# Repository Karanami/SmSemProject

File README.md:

# Piotr Lesicki 151052 - Line Follower

## General description
Line Follower - as it's name implies this robot will realise the task of following the line. 
The robot will consist of two motors, imu, line sensors (white/black color detectors), motor
encoders as well as an external data storage (flash/sd card) for data logging and of coures
it will also have an uC for general control.

## Hardware

### Motors & motor encoders
The robot will use a simple brushed motor with an extended shaft for the encoder feedback

### IMU
A six axis IMU will be used for data logging.

### line sensors
Basic refleted light detectors will be used for estimating where a black line on a white
background is.

### External data storage
A external storage in a form of a chip or a sd card will be used for logging

### uC
An STM32WB55RGVx will be used for the heart of the robot. It will also allow for a bluetooth
communication implementation to be included in the project, making the whole project smaller 
and more compact.

## Line Following task - regulator
The appropriate regulator is yet to be chosen

## Software

### RTOS 
For an easier implementation of software a fitting RTOS will be used. Azure RTOS will be used 
for that since it implements many robust sub-libraries allowing for light-weight aplications,
such as storage (file storage) drivers for external flash/sd cards or usb interfaces allowing
for on slave multiple devices implemantation and much more.
<br/> 

## Examples
- https://forbot.pl/blog/leksykon/robot-typu-linefollower
- https://www.jsumo.com/arduino-pid-based-line-follower-kit1

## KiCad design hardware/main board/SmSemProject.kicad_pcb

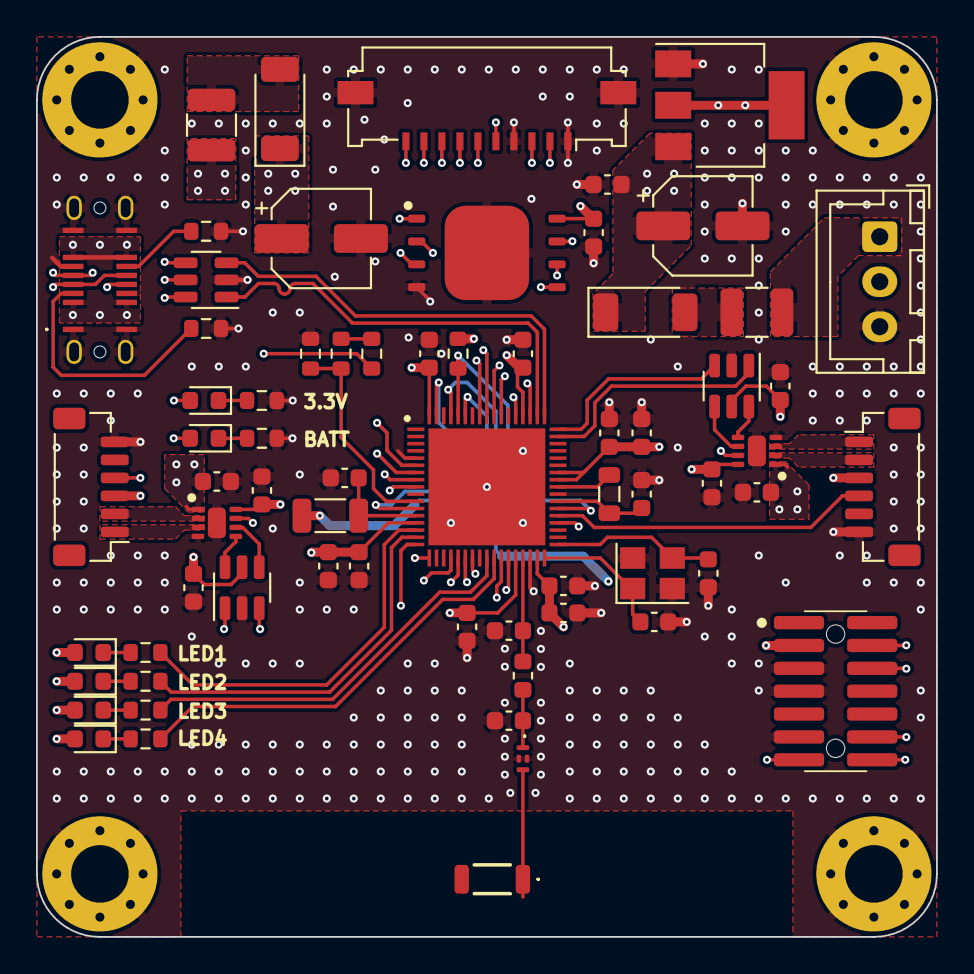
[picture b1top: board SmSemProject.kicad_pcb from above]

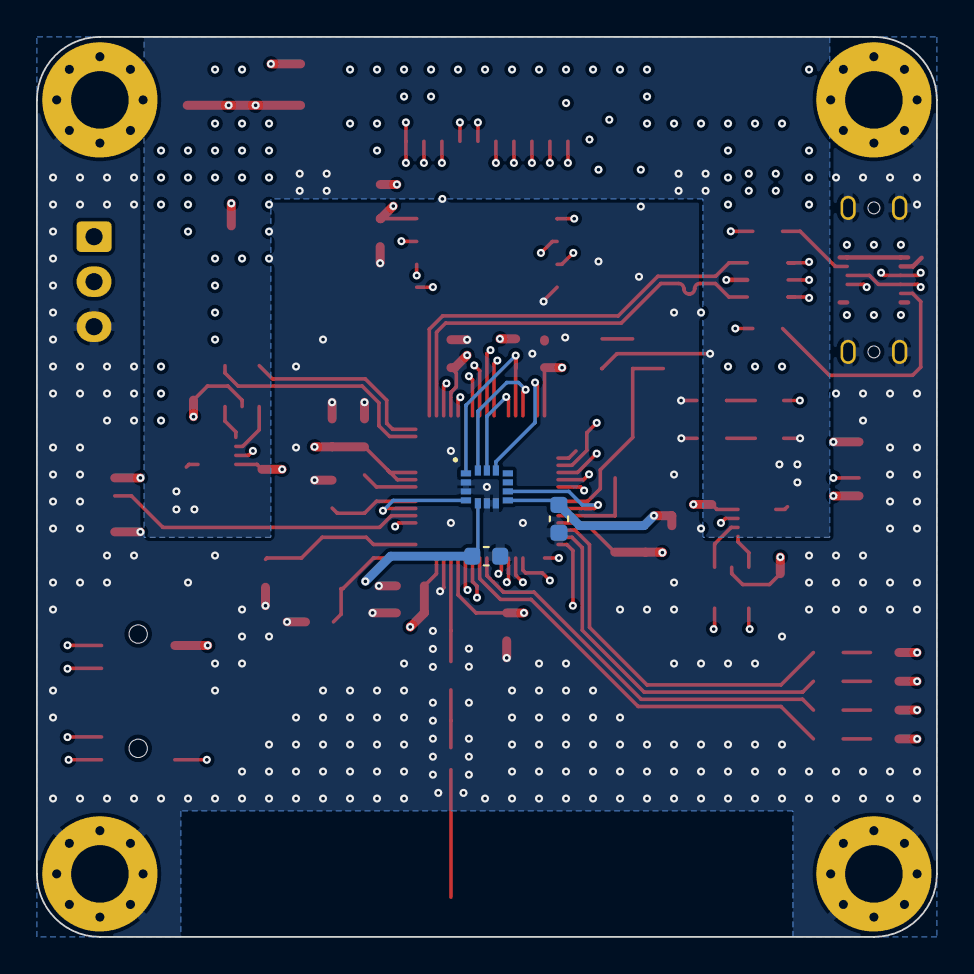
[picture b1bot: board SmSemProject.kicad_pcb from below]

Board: 8 copper layers, 50.0 x 50.0 mm, 74 parts (3 on the bottom side), 69 nets.

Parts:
ANT1: 74889302450
C1, C2: 20pF; C_0603_1608Metric
C3, C4, C5, C9, C11, C16, C19, C25, C26, C27, C28, C30, C31: 100nF; C_0603_1608Metric
C7: 10nF; C_0603_1608Metric
C8: 1uF; C_0603_1608Metric
C10: 100pF; C_0603_1608Metric
C13: 10uF; C_0603_1608Metric
C14, C15, C18, C24: 4.7uF; C_0603_1608Metric
C17, C29: 100uF; CP_Elec_5x4.5
C20: 0.3pF; C_0603_1608Metric
C21: 0.8pF; C_0603_1608Metric
D1, D3: RBS2LAM40CTR; D_SOD-128
D2, D4, D5, D6, D7, D8: LED_Small; LED_0603_1608Metric
F1, F2: 0.5A/16V; Fuse_1210_3225Metric
FL1: DLF162500LT-5028A1; DLF162500LT5028A1
H1, H2, H3, H4: MountingHole_Pad; MountingHole_3.2mm_M3_Pad_Via
IC1: STM32WB55RGV6; QFN40P800X800X100-69N-D
IC2, IC3: DRV8212PDSGR; SON50P200X200X80-9N
IC4: W25N01GVZEIG; SON127P800X600X80-9N-D
IC5: LSM6DSLTR
IC6, IC7: SN74LVC1G18DBVRG4; SOT-23-6
J1, J2: JST-SH 01x06; JST_SH_BM06B-SRSS-TB_1x06-1MP_P1.00mm_Vertical
J3: JST_XH_B3B; JST_XH_B3B-XH-A_1x03_P2.50mm_Vertical
J4: FTSH-107-01-L-DV-K-A; FTSH-107-XX-YYY-DV-K-A
J6: USB4145-03-0070-C; USB4145030070C
J7: Conn_01x10; Molex_200528-0100_1x10-1MP_P1.00mm_Horizontal
L1: 1mH; L_1206_3216Metric
L2: 74479774222; WE-PMI_080562
L3: 2.7nH; L_0603_1608Metric
R1: 1k; R_0603_1608Metric
R2, R3: 5.1k; R_0603_1608Metric
R4, R5, R6, R7, R8, R9, R10, R11, R12: 10k; R_0603_1608Metric
U1: LM1117MP-3.3; SOT-223-3_TabPin2
U2: USBLC6-2SC6; SOT-23-6
Y1: X322516MLB4SI; Crystal_SMD_3225-4Pin_3.2x2.5mm

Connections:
+3.3V: C3.2, C4.2, C5.2, C7.1, C8.1, C9.2, C10.2, C11.2, C15.1, C19.1, C25.1, C26.1, C27.2, C28.2, C30.1, C31.1, D2.2 (A), D4.2 (A), D5.2 (A), D6.2 (A), D7.2 (A), IC1.14 (VDDA), IC1.30 (VDD), IC1.33 (VDDRF), IC1.44 (VDDSMPS), IC1.45 (VDD), IC1.55 (VDDUSB), IC1.68 (VDD), IC2.8 (VCC), IC3.8 (VCC), IC4.8 (VCC), IC5.5 (VDDIO), IC5.8 (VDD), IC6.5 (VCC), IC7.5 (VCC), J1.3, J2.3, J4.3, J7.10, L1.1, R1.1, U1.2 (VO)
+BATT: C16.1, C17.1, C18.1, C24.1, C29.1, D1.1 (K), D3.1 (K), D8.2 (A), IC2.1 (VM), IC3.1 (VM), R9.2, U1.3 (VI)
/ANT_IN: ANT1.1 (FEED), FL1.3 (OUT)
/CONN_D+: J6.A6 (D+), J6.B6 (D+), U2.6 (I/O1)
/CONN_D-: J6.A7 (D-), J6.B7 (D-), U2.4 (I/O2)
/FLT_IN: C21.2, FL1.1 (IN), L3.2
/M_LEFT+: IC2.3 (OUT2), J2.1
/M_LEFT-: IC2.2 (OUT1), J2.2
/M_LEFT_A: IC1.9 (PC0), J2.4
/M_LEFT_DIRECTION: IC1.24 (PA9), IC7.1
/M_LEFT_PWM: IC1.23 (PA8), IC7.3
/M_RIGHT+: IC3.3 (OUT2), J1.1
/M_RIGHT-: IC3.2 (OUT1), J1.2
/M_RIGHT_A: IC1.39 (PB1), J1.4
/M_RIGHT_DIRECTION: IC1.50 (PC6), IC6.1
/M_RIGHT_PWM: IC1.51 (PA10), IC6.3
/Motor Control Left/PWMF: IC2.6 (IN1), IC7.4
/Motor Control Left/PWMR: IC2.5 (IN2), IC7.6
/Motor Control Left/~SLEEP: IC1.38 (PB0), IC2.7 (~SLEEP), IC3.7 (~SLEEP)
/Motor Control Right/PWMF: IC3.6 (IN1), IC6.4
/Motor Control Right/PWMR: IC3.5 (IN2), IC6.6
/SPI_CLK: IC1.63 (PB3), IC5.13 (SCL), J7.5
/SPI_EX_INT1: IC1.60 (PC12), J7.8
/SPI_EX_INT2: IC1.61 (PD0), J7.9
/SPI_MISO: IC1.64 (PB4), IC5.1 (SDO/SA0), J7.2, R1.2
/SPI_MOSI: IC1.65 (PB5), IC5.14 (SDI/SDA), J7.3
/VBUS: F2.1, J6.A4 (VBUS), J6.A9 (VBUS), J6.B4 (VBUS), J6.B9 (VBUS), U2.5 (VBUS)
/VBUSFUSE: D3.2 (A), F2.2
/VCONN: F1.2, J3.1
/VFUSE: D1.2 (A), F1.1
/uC/ANT_OUT: C20.1, IC1.31 (RF1), L3.1
/uC/D+: IC1.53 (PA12), U2.1 (I/O1)
/uC/D-: IC1.52 (PA11), U2.3 (I/O2)
/uC/IMU_INT1: IC1.12 (PC3), IC5.9 (INT2)
/uC/IMU_INT2: IC1.40 (PE4), IC5.4 (INT1)
/uC/LED1: IC1.15 (PA0), R5.1
/uC/LED2: IC1.16 (PA1), R6.1
/uC/LED3: IC1.26 (PC5), R7.1
/uC/LED4: IC1.27 (PB2), R8.1
/uC/OSC_IN: C1.2, IC1.35 (OSC_IN), Y1.3
/uC/OSC_OUT: C2.1, IC1.34 (OSC_OUT), Y1.1
/uC/QSPI_CLK: IC1.18 (PA3), IC4.6 (CLK)
/uC/QSPI_IO0: IC1.7 (PB9), IC4.5 (DI(IO0))
/uC/QSPI_IO1: IC1.6 (PB8), IC4.2 (DO(IO1))
/uC/QSPI_IO2: IC1.22 (PA7), IC4.3 (~WP(IO2))
/uC/QSPI_IO3: IC1.21 (PA6), IC4.7 (~HOLD(IO3))
/uC/SWCLK: IC1.56 (PA14), J4.6
/uC/SWDIO: IC1.54 (PA13), J4.4
/uC/UART_RX: IC1.28 (PB10), J4.13
/uC/UART_TX: IC1.29 (PB11), J4.14
/uC/VBAT: IC1.11 (PC2), R10.2, R11.1
/uC/VFBSMPS: C14.1, IC1.41 (VFBSMPS), L2.2
/uC/VLXSMPS: IC1.43 (VLXSMPS), L2.1
/uC/VREF+: C13.2, IC1.13 (VREF+), L1.2
/uC/~QSPI_CS: IC1.17 (PA2), IC4.1 (~CS)
/uC/~RST: IC1.8 (~RST), J4.12
/uC/~SPI_IMU_CS: IC1.67 (PB7), IC5.12 (~CS)
/~SPI_EX1_CS: IC1.58 (PC10), J7.6
/~SPI_EX2_CS: IC1.59 (PC11), J7.7
GND: C1.1, C2.2, C3.1, C4.1, C5.1, C7.2, C8.2, C9.1, C10.1, C11.1, C13.1, C14.2, C15.2, C16.2, C17.2, C18.2, C19.2, C20.2, C21.1, C24.2, C25.2, C26.2, C27.1, C28.1, C29.2, C30.2, C31.2, FL1.2 (GND), FL1.4 (GND), H1.1, H2.1, H3.1, H4.1, IC1.5 (PH3-BOOT0), IC1.32 (VSSRF), IC1.42 (VSSSMPS), IC1.69 (EP), IC2.4 (GND), IC2.9 (EP), IC3.4 (GND), IC3.9 (EP), IC4.4 (GND), IC4.9 (EP), IC5.2 (SDX), IC5.3 (SCX), IC5.6 (GND), IC5.7 (GND), IC6.2 (GND), IC7.2 (GND), J1.6, J2.6, J3.3, J4.5, J4.7, J4.11, J6.A1 (GND), J6.A8 (SBU1), J6.A12 (GND), J6.B1 (GND), J6.B8 (SBU2), J6.B12 (GND), J6.MH (SHIELD), J7.1, J7.4, J7.MP (MountPin), R2.2, R3.2, R4.1, R10.1, R12.1, U1.1 (GND), U2.2 (GND), Y1.2, Y1.4
unnamed: D2.1 (K), R4.2
unnamed: D4.1 (K), R5.2
unnamed: D5.1 (K), R6.2
unnamed: D6.1 (K), R7.2
unnamed: D7.1 (K), R8.2
unnamed: D8.1 (K), R12.2
unnamed: J6.A5 (CC1), R2.1
unnamed: J6.B5 (CC2), R3.1
unnamed: R9.1, R11.2

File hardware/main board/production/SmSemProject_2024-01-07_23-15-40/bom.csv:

Designator,Footprint,Quantity,Value,LCSC Part #
ANT1,74889302450,1,74889302450,
"C1, C2",0603,2,20pF,
C10,0603,1,100pF,
"C11, C16, C19, C25, C26, C27, C28, C3, C30, C31, C4, C5, C9",0603,13,100nF,
C13,0603,1,10uF,
"C14, C15, C18, C24",0603,4,4.7uF,
"C17, C29",CP_Elec_5x4.5,2,100uF,
C20,0603,1,0.3pF,
C21,0603,1,0.8pF,
C7,0603,1,10nF,
C8,0603,1,1uF,
"D1, D3",D_SOD-128,2,RBS2LAM40CTR,
"D2, D4, D5, D6, D7, D8",0603,6,LED_Small,
"F1, F2",1210,2,0.5A/16V,
FL1,DLF162500LT5028A1,1,DLF162500LT-5028A1,
"H1, H2, H3, H4",MountingHole_3.2mm_M3_Pad_Via,4,MountingHole_Pad,
IC1,QFN40P800X800X100-69N-D,1,STM32WB55RGV6,
"IC2, IC3",SON50P200X200X80-9N,2,DRV8212PDSGR,
IC4,SON127P800X600X80-9N-D,1,W25N01GVZEIG,
IC5,LSM6DSLTR,1,LSM6DSLTR,
"IC6, IC7",SOT-23-6,2,SN74LVC1G18DBVRG4,
"J1, J2",JST_SH_BM06B-SRSS-TB_1x06-1MP_P1.00mm_Vertical,2,JST-SH 01x06,
J3,JST_XH_B3B-XH-A_1x03_P2.50mm_Vertical,1,JST_XH_B3B,
J4,FTSH-107-XX-YYY-DV-K-A,1,FTSH-107-01-L-DV-K-A,
J6,USB4145030070C,1,USB4145-03-0070-C,
J7,Molex_200528-0100_1x10-1MP_P1.00mm_Horizontal,1,Conn_01x10,
L1,1206,1,1mH,
L2,WE-PMI_080562,1,74479774222,
L3,0603,1,2.7nH,
R1,0603,1,1k,
"R10, R11, R12, R4, R5, R6, R7, R8, R9",0603,9,10k,
"R2, R3",0603,2,5.1k,
U1,SOT-223-3_TabPin2,1,LM1117MP-3.3,
U2,SOT-23-6,1,USBLC6-2SC6,
Y1,Crystal_SMD_3225-4Pin_3.2x2.5mm,1,X322516MLB4SI,

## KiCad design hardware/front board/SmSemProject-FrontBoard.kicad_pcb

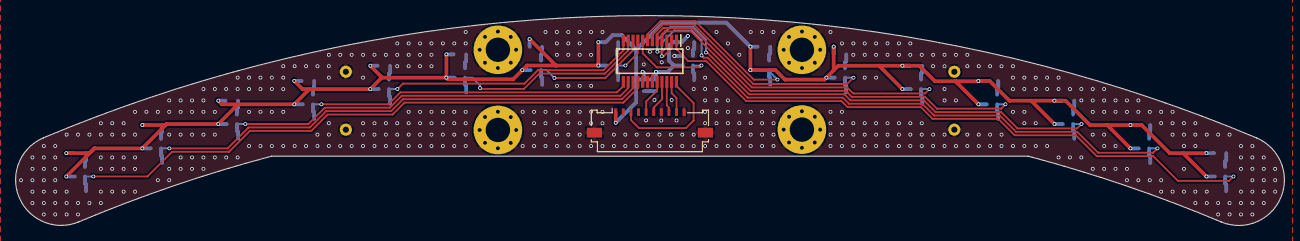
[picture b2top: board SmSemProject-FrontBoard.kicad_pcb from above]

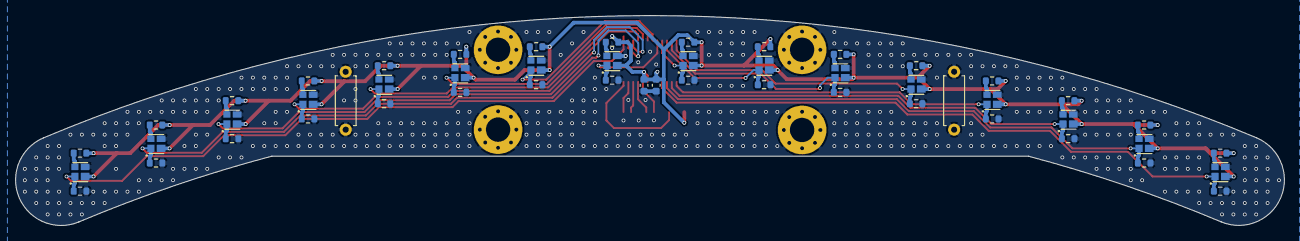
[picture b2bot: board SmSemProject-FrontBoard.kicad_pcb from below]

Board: 2 copper layers, 166.9 x 27.6 mm, 58 parts (52 on the bottom side), 39 nets.

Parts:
C1, C2: 100nF; C_0603_1608Metric
H1, H2, H3, H4: MountingHole_Pad; MountingHole_3.2mm_M3_Pad_Via
IC1, IC3, IC4, IC5, IC6, IC7, IC8, IC9, IC10, IC11, IC12, IC13, IC14, IC15, IC16, IC17: VCNT2020
IC2: MAX11643EEG+; SOP64P602X175-24N
J2: Conn_01x10_MountingPin; Molex_200528-0100_1x10-1MP_P1.00mm_Horizontal
R1, R3, R5, R7, R9, R11, R13, R15, R17, R19, R21, R23, R25, R27, R29, R31: 1k; R_0603_1608Metric
R2, R4, R6, R8, R10, R12, R14, R16, R18, R20, R22, R24, R26, R28, R30, R32: 100; R_0603_1608Metric
R33, R34: --; R_Axial_DIN0207_L6.3mm_D2.5mm_P7.62mm_Horizontal

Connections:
+3.3V: C1.2, C2.2, IC1.2, IC2.17 (REF), IC2.19 (VDD), IC3.2, IC4.2, IC5.2, IC6.2, IC7.2, IC8.2, IC9.2, IC10.2, IC11.2, IC12.2, IC13.2, IC14.2, IC15.2, IC16.2, IC17.2, J2.1, R2.2, R4.2, R6.2, R8.2, R10.2, R12.2, R14.2, R16.2, R18.2, R20.2, R22.2, R24.2, R26.2, R28.2, R30.2, R32.2
/OUT0: IC1.1, IC2.1 (AIN0), R1.1
/OUT1: IC2.2 (AIN1), IC3.1, R3.1
/OUT2: IC2.3 (AIN2), IC4.1, R5.1
/OUT3: IC2.4 (AIN3), IC5.1, R7.1
/OUT4: IC2.5 (AIN4), IC7.1, R11.1
/OUT5: IC2.6 (AIN5), IC8.1, R13.1
/OUT6: IC2.7 (AIN6), IC9.1, R15.1
/OUT7: IC2.8 (AIN7), IC6.1, R9.1
/OUT8: IC2.9 (AIN8), IC11.1, R19.1
/OUT9: IC2.10 (AIN9), IC12.1, R21.1
/OUT10: IC2.11 (AIN10), IC13.1, R23.1
/OUT11: IC2.12 (AIN11), IC10.1, R17.1
/OUT12: IC2.13 (AIN12), IC15.1, R27.1
/OUT13: IC2.14 (AIN13), IC16.1, R29.1
/OUT14: IC2.15 (AIN14), IC17.1, R31.1
/OUT15: IC2.16 (~CNVST/AIN15), IC14.1, R25.1
/SPI_CLK: IC2.21 (SCLK), J2.6
/SPI_EX_INT1: IC2.24 (~EOC), J2.3
/SPI_MISO: IC2.23 (DOUT), J2.9
/SPI_MOSI: IC2.22 (DIN), J2.8
/Sensor0/A: IC1.3 (A), R2.1
/Sensor1/A: IC3.3 (A), R4.1
/Sensor2/A: IC4.3 (A), R6.1
/Sensor3/A: IC5.3 (A), R8.1
/Sensor4/A: IC7.3 (A), R12.1
/Sensor5/A: IC8.3 (A), R14.1
/Sensor6/A: IC9.3 (A), R16.1
/Sensor7/A: IC6.3 (A), R10.1
/Sensor8/A: IC11.3 (A), R20.1
/Sensor9/A: IC12.3 (A), R22.1
/Sensor10/A: IC13.3 (A), R24.1
/Sensor11/A: IC10.3 (A), R18.1
/Sensor12/A: IC15.3 (A), R28.1
/Sensor13/A: IC16.3 (A), R30.1
/Sensor14/A: IC17.3 (A), R32.1
/Sensor15/A: IC14.3 (A), R26.1
/~SPI_EX1_CS: IC2.20 (~CS), J2.5
GND: C1.1, C2.1, H1.1, H2.1, H3.1, H4.1, IC1.4 (K), IC2.18 (GND), IC3.4 (K), IC4.4 (K), IC5.4 (K), IC6.4 (K), IC7.4 (K), IC8.4 (K), IC9.4 (K), IC10.4 (K), IC11.4 (K), IC12.4 (K), IC13.4 (K), IC14.4 (K), IC15.4 (K), IC16.4 (K), IC17.4 (K), J2.7, J2.10, J2.MP (MountPin), R1.2, R3.2, R5.2, R7.2, R9.2, R11.2, R13.2, R15.2, R17.2, R19.2, R21.2, R23.2, R25.2, R27.2, R29.2, R31.2, R33.1, R33.2, R34.1, R34.2

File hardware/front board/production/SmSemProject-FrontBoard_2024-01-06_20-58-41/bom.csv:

Designator,Footprint,Quantity,Value,LCSC Part #
"C1, C2",0603,2,100nF,
"H1, H2, H3, H4",MountingHole_3.2mm_M3_Pad_Via,4,MountingHole_Pad,
"IC1, IC10, IC11, IC12, IC13, IC14, IC15, IC16, IC17, IC3, IC4, IC5, IC6, IC7, IC8, IC9",VCNT2020,16,VCNT2020,
IC2,SOP64P602X175-24N,1,MAX11643EEG+,
J2,Molex_200528-0100_1x10-1MP_P1.00mm_Horizontal,1,Conn_01x10_MountingPin,
"R1, R11, R13, R15, R17, R19, R21, R23, R25, R27, R29, R3, R31, R5, R7, R9",0603,16,1k,
"R10, R12, R14, R16, R18, R2, R20, R22, R24, R26, R28, R30, R32, R4, R6, R8",0603,16,100,
"R33, R34",R_Axial_DIN0207_L6.3mm_D2.5mm_P7.62mm_Horizontal,2,--,

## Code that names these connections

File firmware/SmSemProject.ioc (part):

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Mcu.Name=STM32WB55RGVx
Mcu.Package=VFQFPN68
Mcu.UserName=STM32WB55RGVx
PA0.GPIOParameters=GPIO_PuPd,GPIO_Label,GPIO_ModeDefaultOutputPP
PA0.GPIO_Label=LED1
PA0.GPIO_ModeDefaultOutputPP=GPIO_MODE_OUTPUT_OD
PA0.GPIO_PuPd=GPIO_NOPULL
PA0.Signal=GPIO_Output
PA1.GPIOParameters=GPIO_PuPd,GPIO_Label,GPIO_ModeDefaultOutputPP
PA1.GPIO_Label=LED2
PA1.GPIO_ModeDefaultOutputPP=GPIO_MODE_OUTPUT_OD
PA1.GPIO_PuPd=GPIO_NOPULL
PA1.Signal=GPIO_Output
PA10.GPIOParameters=GPIO_Speed,GPIO_Label
PA10.GPIO_Label=M_RIGHT_PWM
PA10.GPIO_Speed=GPIO_SPEED_FREQ_VERY_HIGH
PA10.Signal=S_TIM1_CH3
PA11.Mode=Device
PA11.Signal=USB_DM
PA12.Mode=Device
PA12.Signal=USB_DP
PA13.Mode=Serial_Wire
PA13.Signal=SYS_JTMS-SWDIO
PA14.Mode=Serial_Wire
PA14.Signal=SYS_JTCK-SWCLK
PA2.GPIOParameters=GPIO_Speed,GPIO_Label
PA2.GPIO_Label=QSPI_NCS
PA2.GPIO_Speed=GPIO_SPEED_FREQ_VERY_HIGH
PA2.Mode=Single Bank 1
PA2.Signal=QUADSPI_BK1_NCS
PA3.GPIOParameters=GPIO_Speed,GPIO_Label
PA3.GPIO_Label=QSPI_CLK
PA3.GPIO_Speed=GPIO_SPEED_FREQ_VERY_HIGH
PA3.Mode=Single Bank 1
PA3.Signal=QUADSPI_CLK
PA6.GPIOParameters=GPIO_Speed,GPIO_Label
PA6.GPIO_Label=QSPI_IO3
PA6.GPIO_Speed=GPIO_SPEED_FREQ_VERY_HIGH
PA6.Mode=Single Bank 1
PA6.Signal=QUADSPI_BK1_IO3
PA7.GPIOParameters=GPIO_Speed,GPIO_Label
PA7.GPIO_Label=QSPI_IO2
PA7.GPIO_Speed=GPIO_SPEED_FREQ_VERY_HIGH
PA7.Mode=Single Bank 1
PA7.Signal=QUADSPI_BK1_IO2
PA8.GPIOParameters=GPIO_Speed,GPIO_Label
PA8.GPIO_Label=M_LEFT_PWM
PA8.GPIO_Speed=GPIO_SPEED_FREQ_VERY_HIGH
PA8.Signal=S_TIM1_CH1
PA9.GPIOParameters=GPIO_Label
PA9.GPIO_Label=M_LEFT_DIRECTION
PA9.Signal=GPIO_Output
PB0.GPIOParameters=GPIO_Label
PB0.GPIO_Label=NM_SLEEP
PB0.Signal=GPIO_Output
PB1.GPIOParameters=GPIO_PuPd,GPIO_Label
PB1.GPIO_Label=M_RIGHT_A
PB1.GPIO_PuPd=GPIO_PULLUP
PB1.Mode=Counts_external_clock_standalone_1X_occur1
PB1.Signal=LPTIM2_IN1
PB10.GPIOParameters=GPIO_Speed,GPIO_Label
PB10.GPIO_Label=UART_RX
PB10.GPIO_Speed=GPIO_SPEED_FREQ_VERY_HIGH
PB10.Mode=Asynchronous
PB10.Signal=LPUART1_RX
PB11.GPIOParameters=GPIO_Speed,GPIO_Label
PB11.GPIO_Label=UART_TX
PB11.GPIO_Speed=GPIO_SPEED_FREQ_VERY_HIGH
PB11.Mode=Asynchronous
PB11.Signal=LPUART1_TX
PB2.GPIOParameters=GPIO_PuPd,GPIO_Label,GPIO_ModeDefaultOutputPP
PB2.GPIO_Label=LED4
PB2.GPIO_ModeDefaultOutputPP=GPIO_MODE_OUTPUT_OD
PB2.GPIO_PuPd=GPIO_NOPULL
PB2.Signal=GPIO_Output
PB3.GPIOParameters=GPIO_Speed,GPIO_Label
PB3.GPIO_Label=SPI_SCK
PB3.GPIO_Speed=GPIO_SPEED_FREQ_VERY_HIGH
PB3.Mode=Full_Duplex_Master
PB3.Signal=SPI1_SCK
PB4.GPIOParameters=GPIO_Speed,GPIO_Label
PB4.GPIO_Label=SPI_MOSI
PB4.GPIO_Speed=GPIO_SPEED_FREQ_VERY_HIGH
PB4.Mode=Full_Duplex_Master
PB4.Signal=SPI1_MISO
PB5.GPIOParameters=GPIO_Speed,GPIO_Label
PB5.GPIO_Label=SPI_MISO
PB5.GPIO_Speed=GPIO_SPEED_FREQ_VERY_HIGH
PB5.Mode=Full_Duplex_Master
PB5.Signal=SPI1_MOSI
PB7.GPIOParameters=PinState,GPIO_Label
PB7.GPIO_Label=SPI_IMU_NCS
PB7.PinState=GPIO_PIN_SET
PB7.Signal=GPIO_Output
PB8.GPIOParameters=GPIO_Speed,GPIO_Label
PB8.GPIO_Label=QSPI_IO1
PB8.GPIO_Speed=GPIO_SPEED_FREQ_VERY_HIGH
PB8.Mode=Single Bank 1
PB8.Signal=QUADSPI_BK1_IO1
PB9.GPIOParameters=GPIO_Speed,GPIO_Label
PB9.GPIO_Label=QSPI_IO0
PB9.GPIO_Speed=GPIO_SPEED_FREQ_VERY_HIGH
PB9.Mode=Single Bank 1
PB9.Signal=QUADSPI_BK1_IO0
PC0.GPIOParameters=GPIO_Label
PC0.GPIO_Label=M_LEFT_PWM
PC0.Mode=Counts_external_clock_standalone_1X_occur1
PC0.Signal=LPTIM1_IN1
PC10.GPIOParameters=PinState,GPIO_Label
PC10.GPIO_Label=SPI_EX_NCS1
PC10.PinState=GPIO_PIN_SET
PC10.Signal=GPIO_Output
PC11.GPIOParameters=PinState,GPIO_Label
PC11.GPIO_Label=SPI_EX_NCS2
PC11.PinState=GPIO_PIN_SET
PC11.Signal=GPIO_Output
PC12.GPIOParameters=GPIO_Label
PC12.GPIO_Label=SPI_EX_INT1
PC12.Signal=GPXTI12
PC2.GPIOParameters=GPIO_Label
PC2.GPIO_Label=VBAT
PC2.Signal=ADCx_IN3
PC3.GPIOParameters=GPIO_Label
PC3.GPIO_Label=SPI_IMU_INT1
PC3.Signal=GPXTI3
PC5.GPIOParameters=GPIO_PuPd,GPIO_Label,GPIO_ModeDefaultOutputPP
PC5.GPIO_Label=LED3
PC5.GPIO_ModeDefaultOutputPP=GPIO_MODE_OUTPUT_OD
PC5.GPIO_PuPd=GPIO_NOPULL
PC5.Signal=GPIO_Output
PC6.GPIOParameters=GPIO_Label
PC6.GPIO_Label=M_RIGHT_DIRECTION
PC6.Signal=GPIO_Output
PD0.GPIOParameters=GPIO_Label
PD0.GPIO_Label=SPI_EX_INT2
PD0.Signal=GPXTI0
PE4.GPIOParameters=GPIO_Label
PE4.GPIO_Label=SPI_IMU_INT2
PE4.Signal=GPXTI4
RCC.HSE_VALUE=32000000
RCC.SYSCLKFreq_VALUE=64000000
RCC.SYSCLKSource=RCC_SYSCLKSOURCE_PLLCLK
board=custom

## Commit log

2023-12-16 init commit
2023-12-17 uC change"
2023-12-20 sync, migrate to newest IDE
2023-12-21 project synopis update (README)
2024-01-04 schematic progress has been made
2024-01-05 main board done, added front board projec
2024-01-06 front board schematic done
2024-01-06 front board layout & routing mostly done
2024-01-07 all layouts and routings done
2024-01-07 tuned lenghts of signals with higher frequencies
2024-01-12 firmware - added common classes
2024-01-12 sync
2024-01-13 frimware
2024-01-13 spi_api
2024-01-17 queue peek function
2024-01-25 changed to freertos
